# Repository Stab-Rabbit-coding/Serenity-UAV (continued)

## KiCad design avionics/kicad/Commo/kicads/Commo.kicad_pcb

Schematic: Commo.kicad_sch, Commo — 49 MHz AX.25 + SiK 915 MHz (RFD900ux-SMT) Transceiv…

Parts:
1.2k C: 10nF RX RC Bandpass 1200Hz Cap
1.2k R: 13k Ohm RX RC Bandpass 1200Hz
2.2k C: 10nF RX RC Bandpass 2200Hz Cap
2.2k R: 7.2k Ohm RX RC Bandpass 2200Hz
49M DDS: Si5351A-B-GT 49MHz DDS I2C Synthesiser
+3V 10n: 10nF C0G 0402 +3V3 VHF 49MHz Bypass
+3V 10u: 10uF X5R 0805 +3V3 Mid-freq
+3V 100n: 100nF X7R 0402 +3V3 HF Bypass
+3V 100u: 100uF 10V X5R 1210 +3V3 Bulk
+5V 100n: 100nF X7R 0402 +5V HF Bypass
+5V 100u: 100uF 10V X5R 1210 +5V Bulk
+5V Bead: 742792512
AFSK Cp: 1uF AFSK Audio Coupling DAC→PA
ANT CMC: SRF2012-100Y
ANT RPSMA: RPSMA-EDGE-50R
ANT TVS: PRTR5V0U2X; SOT-143
C1 120p: 120pF C0G LPF Shunt-1
C2 180p: 180pF C0G LPF Shunt-2
C3 120p: 120pF C0G LPF Shunt-3
C-SIK1: 10uF 10V X5R
C-SIK2: 100nF
C-SIK-SH1, C-SIK-SH2: DNP
CMP By: 100nF +3V3 U2B CMP Bypass
C_INV: 100nF C0G 0402 INV1 VCC Bypass
C_MUX: 100nF C0G 0402 MUX1 VCC Bypass
C_TPM_EMMA1: 100nF; C_0402_1005Metric
D-ANT-SIK: ESD101-B1-02ELS; Infineon_TSSLP-2-4_0.62x0.32mm
DAC By: 100nF +3V3 U2A DAC Bypass
ETH-PHY: ADIN1300BCPZ
GND X2Y: 4.7nF_X2Y_C0G
INV1: SN74LVC1G04 SOT-23-5 3.3V UART_RX_F->SBUS_OUT
J-ANT-SIK: MMCX vertical
J-ETH: JST-GH-4P-ETH
L1 100n: 100nH Coilcraft-0805HQ-101J LPF Series-1
L2 180n: 180nH Coilcraft-0805HQ-181J LPF Series-2
L3 180n: 180nH Coilcraft-0805HQ-181J LPF Series-3
L-SIK-SER: 0R link
LDO 3V3: MCP1703T-3302 LDO 3.3V 72dB-PSRR@100kHz
LDO By: 100nF +3V3 U6 LDO Bypass
LNA: MGA-82563 LNA 2.4dB NF 50-6000MHz
LNA By: 100nF +3V3 U4 LNA Bypass
MUX1: SN74LVC1G3157DRYR; Texas_USON-6_1x1.45mm_P0.5mm_SMD
OSC By: 100nF +3V3 X1 TCXO Bypass
PA 100mW: 2N3866 NPN BJT PA Class-AB Final 100mW
PA By: 100nF +5V U3 PA VCC Bypass
PA By2: 1nF U3B Collector RF Bypass
PA Cb1: 100pF DDS-RF Coupling Cap to U3A
PA Cb2: 100pF PA Interstage Bypass
PA Drvr: PMBT2222A,215; SOT-23
PA Rb1: 10k Ohm U3A Base Bias Resistor
PA Rb2: 1k Ohm U3B Base Bias Resistor
PA Rc1: 100 Ohm U3A Collector Load
PA Re: 10 Ohm U3B Emitter Degeneration
PB2-P1: PB2I-P1-2x18
PB2-P2: PB2I-P2-2x18
PGND 10n: 10nF C0G 0402 GND-PGND Moat Bridge
PTT Bead: 742792510 0402 Ferrite Bead 600Ohm@100MHz
RSSI Hi: 10k Ohm RSSI Scale Upper
RSSI Lo: 10k Ohm RSSI Scale Lower
RSSI_CBY: 100nF RSSI_CMP VCC Bypass
RSSI_CMP: LMV331 RSSI Carrier-Detect Comparator
RSSI_RH: 100k RSSI DCD Threshold Upper
RSSI_RL: 100k RSSI DCD Threshold Lower
RX Bead: 742792510 0402 Ferrite Bead 600Ohm@100MHz
RX Demod: LM393 Comparator RX-AFSK Demodulator
R_MODE: 10k Ohm MODE_SEL Pull-Down UART=default
R_TPM_RST_EMMA: 10k; R_0402_1005Metric
S1: SPST-SMD OPEN=UART CLOSED=SBUS
SIK: RFD900ux-SMT
SMA ESD: SMAJ5.0A Bidirectional TVS 5V Antenna ESD
SW By: 100nF +3V3 U5 Switch Bypass
T-ETH: 749010012A
T/R Sw: PE4259-63 SPDT TX/RX Switch ≥35dB isolation
TCXO 25M: TG2520SMN 25MHz TCXO ±0.5ppm
TPM: Infineon SLB9672 TPM2.0; QFN-32-1EP_5x5mm_P0.5mm_EP3.45x3.45mm
TX Bead: 742792510 0402 Ferrite Bead 600Ohm@100MHz
TX DAC: MCP4921 12-bit SPI DAC TX-AFSK Audio
Th Hi: 10k Ohm LM393 Threshold Upper
Th Lo: 10k Ohm LM393 Threshold Lower
U1 ByA: 100nF +3V3 U1-VDDA Bypass
U1 ByB: 100nF +3V3 U1-VDD Bypass
UART CMC: SRF2012-100Y CMC UART TX/RX Pair 10uH
UART TVS: PRTR5V0U2X; SOT-143

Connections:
+3V3: 49M DDS.1 (+3V3), 49M DDS.10 (+3V3), +3V 10n.1 (+3V3), +3V 10u.1 (+3V3), +3V 100n.1 (+3V3), +3V 100u.1 (+3V3), CMP By.1 (+3V3), C_INV.1 (+3V3), C_MUX.1 (+3V3), C_TPM_EMMA1.1, DAC By.1 (+3V3), INV1.4 (+3V3), LDO 3V3.3 (+3V3), LDO 3V3.4 (+3V3), LDO By.1 (+3V3), LNA.4 (+3V3), LNA By.1 (+3V3), MUX1.5 (VCC), OSC By.1 (+3V3), PB2-P1.33 (+3V3), PB2-P1.34 (+3V3), RSSI_CBY.1 (+3V3), RSSI_CMP.2 (+3V3), RSSI_RH.1 (+3V3), RX Demod.2 (+3V3), R_TPM_RST_EMMA.1, S1.1 (+3V3), SW By.1 (+3V3), TCXO 25M.1 (+3V3), TCXO 25M.4 (+3V3), TPM.1 (VDD), TPM.8 (NCI/VDD), TPM.14 (VDD), TPM.22 (VDD), TX DAC.1 (+3V3), TX DAC.6 (+3V3), Th Hi.1 (+3V3), U1 ByA.1 (+3V3), U1 ByB.1 (+3V3)
+5V: +5V Bead.1 (+5V), PB2-P1.35 (+5V), PB2-P2.35 (+5V)
+5V_FILT: +5V 100n.1 (+5V_FILT), +5V 100u.1 (+5V_FILT), +5V Bead.2 (+5V_FILT), LDO 3V3.1 (+5V_FILT), PA By.1 (+5V_FILT), PA Rb1.1 (+5V_FILT), PA Rc1.1 (+5V_FILT)
AFSK_IN: AFSK Cp.2 (AFSK_IN), RX Demod.1 (AFSK_IN)
AFSK_OUT: AFSK Cp.1 (AFSK_OUT), TX DAC.7 (AFSK_OUT)
ANT: ANT CMC.1, ANT CMC.2, ANT RPSMA.1 (ANT), ANT TVS.2 (IO1), SMA ESD.1 (ANT), T/R Sw.1 (ANT)
COMP_IN: 1.2k C.1 (COMP_IN), 1.2k R.2 (COMP_IN), 2.2k C.1 (COMP_IN), 2.2k R.2 (COMP_IN), RX Demod.3 (COMP_IN), Th Lo.1 (COMP_IN)
DDS_CLK: 49M DDS.6 (DDS_CLK), TX DAC.3 (DDS_CLK)
DDS_DAT: 49M DDS.7 (DDS_DAT), TX DAC.4 (DDS_DAT)
DDS_FSYNC: PB2-P1.26 (DDS_FSYNC), TX DAC.2 (DDS_FSYNC)
DDS_RF: 49M DDS.3 (DDS_RF), PA Cb1.1 (DDS_RF), PA Drvr.1 (B), PA Rb1.2 (DDS_RF)
EMMA_ETH_LINE_RXN: J-ETH.4 (EMMA_ETH_LINE_RXN), T-ETH.8 (EMMA_ETH_LINE_RXN)
EMMA_ETH_LINE_RXP: J-ETH.3 (EMMA_ETH_LINE_RXP), T-ETH.7 (EMMA_ETH_LINE_RXP)
EMMA_ETH_LINE_TXN: J-ETH.2 (EMMA_ETH_LINE_TXN), T-ETH.6 (EMMA_ETH_LINE_TXN)
EMMA_ETH_LINE_TXP: J-ETH.1 (EMMA_ETH_LINE_TXP), T-ETH.5 (EMMA_ETH_LINE_TXP)
EMMA_ETH_RXN: ETH-PHY.5 (EMMA_ETH_RXN), T-ETH.4 (EMMA_ETH_RXN)
EMMA_ETH_RXP: ETH-PHY.4 (EMMA_ETH_RXP), T-ETH.3 (EMMA_ETH_RXP)
EMMA_ETH_TXN: ETH-PHY.2 (EMMA_ETH_TXN), T-ETH.2 (EMMA_ETH_TXN)
EMMA_ETH_TXP: ETH-PHY.1 (EMMA_ETH_TXP), T-ETH.1 (EMMA_ETH_TXP)
GND: 1.2k C.2 (GND), 2.2k C.2 (GND), 49M DDS.2 (GND), 49M DDS.4 (GND), 49M DDS.5 (GND), 49M DDS.9 (GND), +3V 10n.2 (GND), +3V 10u.2 (GND), +3V 100n.2 (GND), +3V 100u.2 (GND), +5V 100n.2 (GND), +5V 100u.2 (GND), ANT RPSMA.2 (GND), ANT RPSMA.3 (GND), ANT TVS.1 (GND), ANT TVS.4 (VCC), C1 120p.2 (GND), C2 180p.2 (GND), C3 120p.2 (GND), C-SIK1.2 (N), C-SIK2.2 (N), C-SIK-SH1.2 (B), C-SIK-SH2.2 (B), CMP By.2 (GND), C_INV.2 (GND), C_MUX.2 (GND), C_TPM_EMMA1.2, D-ANT-SIK.2 (A2), DAC By.2 (GND), ETH-PHY.3 (GND), ETH-PHY.6 (GND), ETH-PHY.10 (GND), ETH-PHY.11 (GND), ETH-PHY.12 (GND), ETH-PHY.49 (GND), GND X2Y.1, GND X2Y.2, INV1.2 (GND), J-ANT-SIK.2 (SHIELD), LDO 3V3.2 (GND), LDO 3V3.5 (GND), LDO By.2 (GND), LNA.5 (GND), LNA.6 (GND), LNA By.2 (GND), MUX1.2 (GND), OSC By.2 (GND), PA By.2 (GND), PA By2.2 (GND), PA Cb2.2 (GND), PA Drvr.2 (E), PA Re.2 (GND), PB2-P1.1 (GND), PB2-P1.2 (GND), PB2-P1.36 (GND), PB2-P2.36 (GND), PGND 10n.1, PGND 10n.2, RSSI Lo.2 (GND), RSSI_CBY.2 (GND), RSSI_CMP.4 (GND), RSSI_RL.2 (GND), RX Demod.4 (GND), RX Demod.5 (GND), R_MODE.2 (GND), SIK.8 (GND), SIK.9 (GND), SIK.11 (GND), SIK.12 (GND), SIK.14 (GND), SIK.15 (GND), SIK.17 (GND), SIK.18 (GND), SIK.20 (GND), SIK.29 (GND), SIK.30 (GND), SMA ESD.2 (GND), SW By.2 (GND), T/R Sw.2 (GND), T/R Sw.6 (GND), TCXO 25M.2 (GND), TPM.2 (GND), TPM.9 (GND), TPM.16 (NCI/GND), TPM.23 (GND), TPM.32 (GND), TX DAC.5 (GND), TX DAC.8 (GND), Th Hi.2 (GND), Th Lo.2 (GND), U1 ByA.2 (GND), U1 ByB.2 (GND), UART TVS.1 (GND), UART TVS.4 (VCC)
GND2_ETH: ETH-PHY.21 (GND2_ETH), ETH-PHY.22 (GND2_ETH), ETH-PHY.25 (GND2_ETH), ETH-PHY.34 (GND2_ETH), ETH-PHY.36 (GND2_ETH)
MDC: ETH-PHY.19 (MDC), PB2-P2.18 (MDC)
MDIO: ETH-PHY.18 (MDIO), PB2-P2.17 (MDIO)
MODE_SEL: MUX1.6 (S), R_MODE.1 (MODE_SEL), S1.2 (MODE_SEL)
PA_EMIT: PA 100mW.2 (GND), PA Re.1 (PA_EMIT)
PA_INT: PA 100mW.1 (PA_INT), PA Cb1.2 (PA_INT), PA Cb2.1 (PA_INT), PA Drvr.3 (C), PA Rb2.1, PA Rb2.2, PA Rc1.2 (PA_INT)
PHY2_INTRN: ETH-PHY.20 (PHY2_INTRN), PB2-P2.14 (PHY2_INTRN)
PHY2_RSTN: ETH-PHY.35 (PHY2_RSTN), PB2-P2.13 (PHY2_RSTN)
PTT_N: PB2-P2.1 (PTT_N), PTT Bead.1, PTT Bead.2, T/R Sw.4 (PTT_N)
RF_FILT: C3 120p.1 (RF_FILT), L3 180n.2 (RF_FILT), T/R Sw.5 (RF_FILT)
RF_LPF_N1: C1 120p.1 (RF_LPF_N1), L1 100n.2 (RF_LPF_N1), L2 180n.1 (RF_LPF_N1)
RF_LPF_N2: C2 180p.1 (RF_LPF_N2), L2 180n.2 (RF_LPF_N2), L3 180n.1 (RF_LPF_N2)
RF_RX: LNA.3 (RF_RX), T/R Sw.3 (RF_RX)
RF_TX: ANT TVS.3 (IO2), L1 100n.1 (RF_TX), PA 100mW.3 (RF_TX), PA By2.1 (RF_TX)
RMII1_CRS_DV: ETH-PHY.32 (RMII1_CRS_DV), PB2-P2.21 (RMII1_CRS_DV)
RMII1_REF_CLK: ETH-PHY.29 (RMII1_REF_CLK), PB2-P2.19 (RMII1_REF_CLK)
RMII1_RXD0: ETH-PHY.30 (RMII1_RXD0), PB2-P2.23 (RMII1_RXD0)
RMII1_RXD1: ETH-PHY.31 (RMII1_RXD1), PB2-P2.22 (RMII1_RXD1)
RMII1_RX_ER: ETH-PHY.33 (RMII1_RX_ER), PB2-P2.20 (RMII1_RX_ER)
RMII1_TXD0: ETH-PHY.28 (RMII1_TXD0), PB2-P2.26 (RMII1_TXD0)
RMII1_TXD1: ETH-PHY.27 (RMII1_TXD1), PB2-P2.25 (RMII1_TXD1)
RMII1_TX_EN: ETH-PHY.26 (RMII1_TX_EN), PB2-P2.24 (RMII1_TX_EN)
RSSI_ANA: RSSI Hi.2 (RSSI_ANA), RSSI Lo.1 (RSSI_ANA), RSSI_CMP.1 (RSSI_ANA)
RSSI_DCD: PB2-P2.2 (RSSI_DCD), RSSI_CMP.5 (RSSI_DCD)
RSSI_RAW: LNA.2 (RSSI_RAW), RSSI Hi.1 (RSSI_RAW)
RSSI_REF: RSSI_CMP.3 (RSSI_REF), RSSI_RH.2 (RSSI_REF), RSSI_RL.1 (RSSI_REF)
RX_LNA: 1.2k R.1 (RX_LNA), 2.2k R.1 (RX_LNA), LNA.1 (RX_LNA)
SBUS_OUT: INV1.3 (SBUS_OUT), MUX1.1 (B2)
SIK_ANT_F: C-SIK-SH2.1 (A), D-ANT-SIK.1 (A1), J-ANT-SIK.1 (RF), L-SIK-SER.2 (B)
SIK_ANT_RF: C-SIK-SH1.1 (A), L-SIK-SER.1 (A), SIK.13 (SIK_ANT_RF)
SIK_CTS: PB2-P1.20 (LORA_DIO0), SIK.28 (SIK_CTS)
SIK_RTS: PB2-P1.19 (LORA_RESETN), SIK.27 (SIK_RTS)
SIK_VCC: C-SIK1.1, C-SIK2.1, SIK.19 (SIK_VCC)
SPI1_CLK: PB2-P1.25 (SPI1_CLK), TPM.19 (SCLK)
SPI1_CS_TPM: PB2-P1.21 (SPI1_CS_TPM), TPM.20 (CS#)
SPI1_MISO: PB2-P1.23 (SPI1_MISO), TPM.24 (MISO)
SPI1_MOSI: PB2-P1.24 (SPI1_MOSI), TPM.21 (MOSI)
TCXO_OUT: 49M DDS.8 (TCXO_OUT), TCXO 25M.3 (TCXO_OUT)
TPM_IRQN: PB2-P2.12 (TPM_IRQN), TPM.18 (PIRQ#)
TPM_RSTN: PB2-P2.11 (TPM_RSTN), R_TPM_RST_EMMA.2, TPM.17 (RST#)
UART_49MHZ_XCVR_RX: PB2-P1.15 (UART_49MHZ_XCVR_RX), UART CMC.1 (UART_49MHZ_XCVR_RX), UART TVS.2 (IO1)
UART_49MHZ_XCVR_TX: PB2-P1.16 (UART_49MHZ_XCVR_TX), UART CMC.4 (UART_49MHZ_XCVR_TX), UART TVS.3 (IO2)
UART_RX_F: INV1.1 (UART_RX_F), MUX1.3 (B1), RX Bead.1, RX Bead.2
UART_RX_MUX: MUX1.4 (A), UART CMC.3 (UART_RX_MUX)
UART_SIK_RX: PB2-P1.17 (UART_SIK_RX), SIK.25 (UART_SIK_RX)
UART_SIK_TX: PB2-P1.18 (UART_SIK_TX), SIK.26 (UART_SIK_TX)
UART_TX_F: TX Bead.1, TX Bead.2, UART CMC.2 (UART_TX_F)
VCC2_ETH: ETH-PHY.7 (VCC2_ETH), ETH-PHY.8 (VCC2_ETH), ETH-PHY.9 (VCC2_ETH), ETH-PHY.40 (VCC2_ETH), ETH-PHY.41 (VCC2_ETH)

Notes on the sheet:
POWER SUPPLY (5V input filter, MCP1703 LDO, bypass cascade)
DDS / TCXO (Si5351A 49 MHz synthesiser)
PA CHAIN (MMBT2222A driver + 2N3866 100 mW final)
6-ELEMENT CHEBYSHEV LPF
T/R SWITCH, LNA, ANTENNA PORT
AFSK MODEM (MCP4921 TX DAC, LM393 RX demod, tone filters)
UART / SBUS DIGITAL (CMC, TVS, beads, inverter, mux)
RSSI CARRIER-DETECT (NEW 2026-07-04 — analog RSSI -> 1-bit RSSI_DCD)
SiK RFD900ux-SMT (915 MHz UHF telemetry -- relocated from XO 2026-09-21, see avionics/WBS.md)
ETHERNET 2nd PORT (ADIN1300 PHY + T-ETH isolation xfmr, JST-GH-4P line)
PB2-I PASSTHROUGH RAILS (PocketBeagle 2 Industrial P1 + P2)
=== Section: TPM (SLB9672, added 2026-07-26; binds to the PB2-I host -- SPI1 shared bus + TPM_IRQN/TPM_RSTN via P1/P2, no dedicated header) ===
WÜRTH ELEKTRONIK USAGE NOTICE (verbatim, 749010012A data sheet rev 004.000 p.1; applies to Würth parts on this board: 749010012A, 742792510, 742792512): This electronic component has been designed and developed for usage in general electronic equipment only. This product is not authorized for use i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

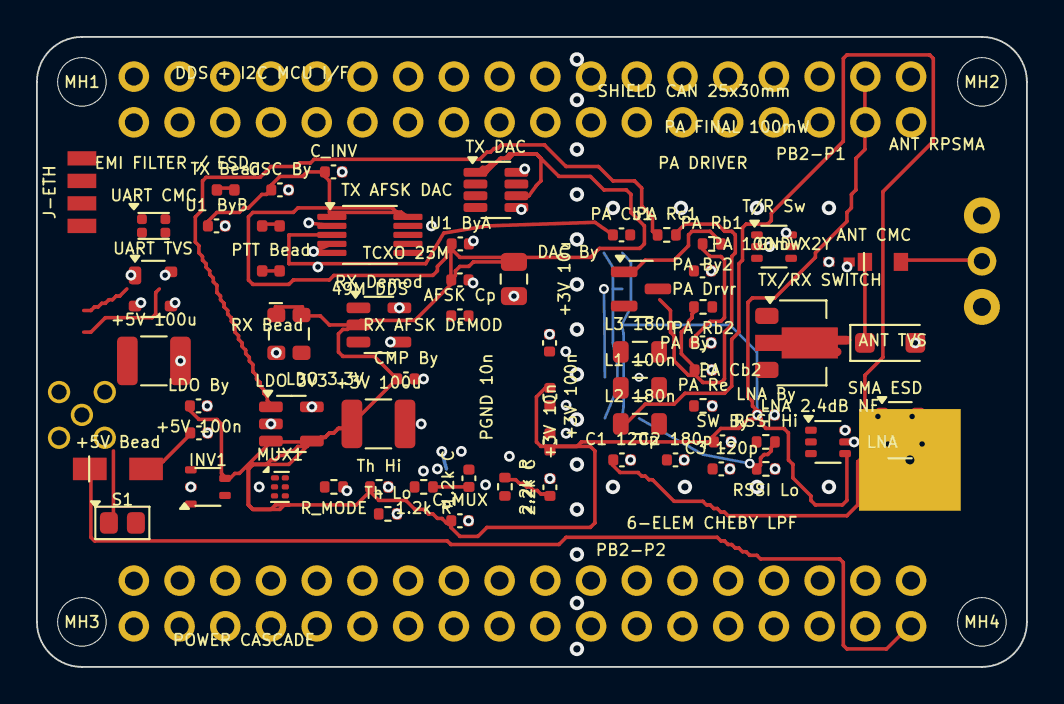
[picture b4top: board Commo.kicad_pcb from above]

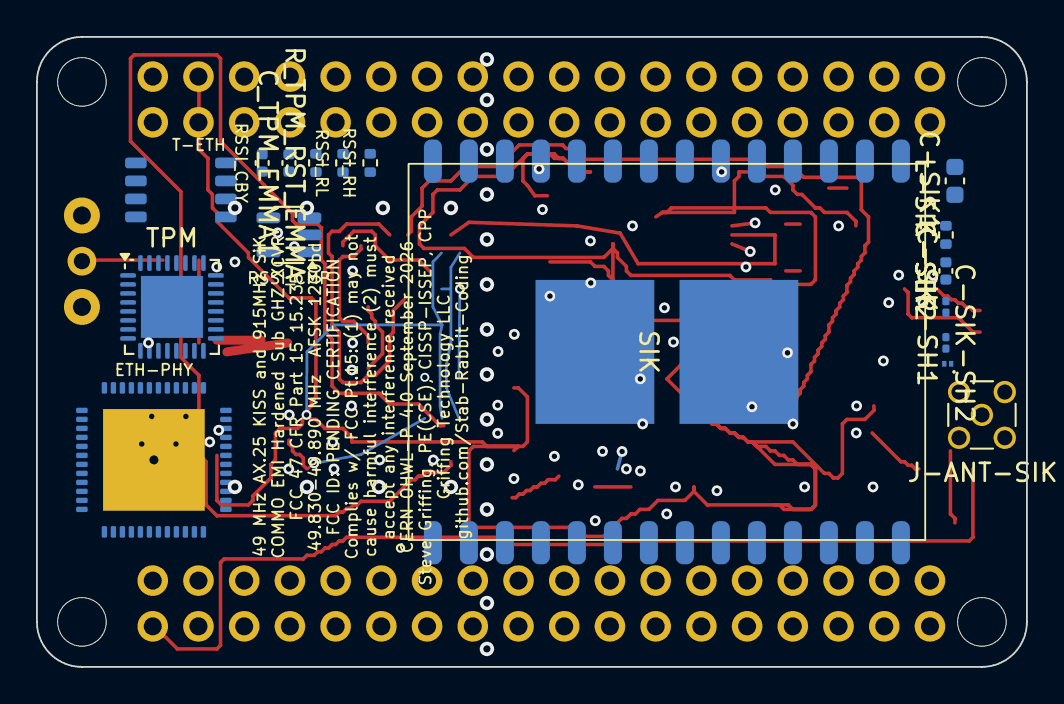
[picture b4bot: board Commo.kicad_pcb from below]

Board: 4 copper layers, 55.0 x 35.0 mm, 88 parts (17 on the bottom side), 68 nets.

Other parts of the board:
MH1, MH2, MH3, MH4: MountingHole_2.7mm_M2.5

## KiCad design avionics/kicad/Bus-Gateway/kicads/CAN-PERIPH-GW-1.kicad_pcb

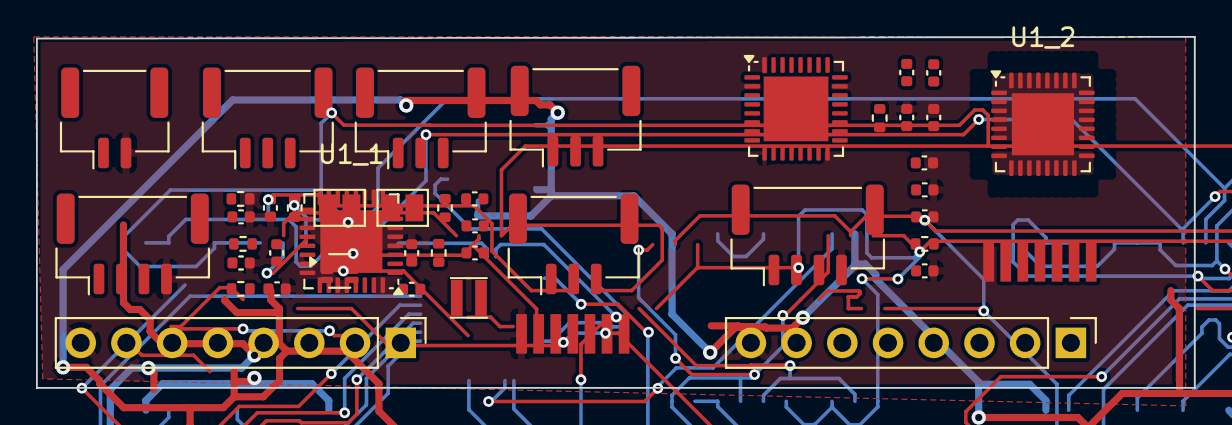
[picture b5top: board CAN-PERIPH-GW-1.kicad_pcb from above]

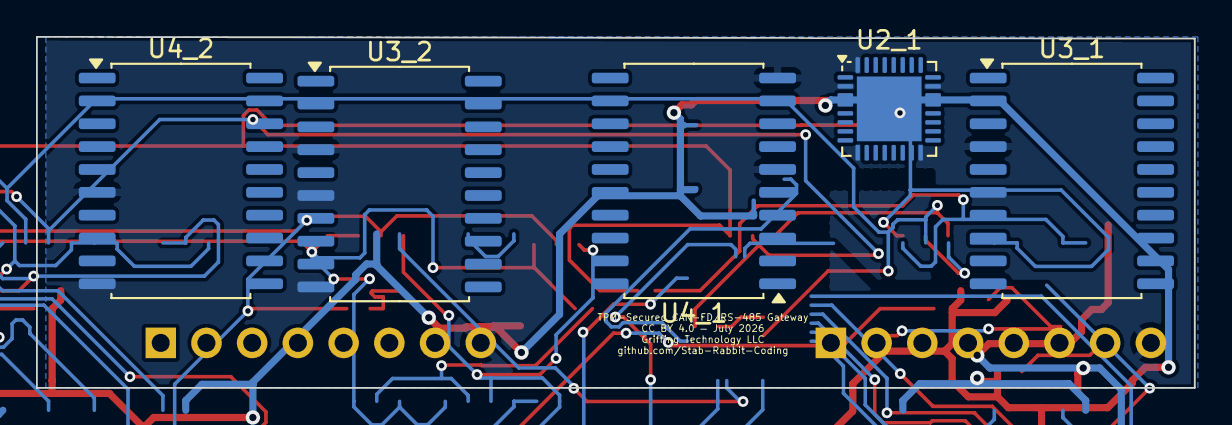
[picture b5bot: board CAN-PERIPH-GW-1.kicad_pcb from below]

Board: 2 copper layers, 64.3 x 19.5 mm, 49 parts (6 on the bottom side), 71 nets.

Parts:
C_IN: 10uF; C_0402_1005Metric
C_ISO1_1, C_ISO1_2: 100nF; C_0402_1005Metric
C_ISO2_1, C_ISO2_2: 1uF; C_0402_1005Metric
C_MCU1_1, C_MCU1_2: 100nF; C_0402_1005Metric
C_OUT: 22uF; C_0402_1005Metric
C_RS1_1, C_RS1_2, C_RS2_1, C_RS2_2: 100nF; C_0402_1005Metric
C_TPM1_1, C_TPM1_2: 100nF; C_0402_1005Metric
C_TPM2_1, C_TPM2_2: 1uF; C_0402_1005Metric
C_VCORE_1, C_VCORE_2: 1uF; C_0402_1005Metric
J_CAN_IN: CAN-FD IN; JST_GH_BM03B-GHS-TBT_1x03-1MP_P1.25mm_Vertical
J_CAN_OUT: CAN-FD OUT; JST_GH_BM03B-GHS-TBT_1x03-1MP_P1.25mm_Vertical
J_ENC_1, J_ENC_2: AK7455 pigtail; Pigtail_7W_DirectSolder
J_FLEX_1, J_FLEX_2: UART/TTL/PWM/BSHOT; PinHeader_1x08_P2.54mm_Vertical
J_PWR: +5V/GND; JST_GH_BM02B-GHS-TBT_1x02-1MP_P1.25mm_Vertical
J_RS485_IN: RS485 IN; JST_GH_BM03B-GHS-TBT_1x03-1MP_P1.25mm_Vertical
J_RS485_OUT: RS485 OUT; JST_GH_BM03B-GHS-TBT_1x03-1MP_P1.25mm_Vertical
J_SWD_1, J_SWD_2: SWD; JST_GH_BM04B-GHS-TBT_1x04-1MP_P1.25mm_Vertical
L1: 2.2uH; L_Taiyo-Yuden_NR-20xx
R_485TERM: 120R; R_0402_1005Metric
R_CANTERM: 120R; R_0402_1005Metric
R_FBB: 100k 1%; R_0402_1005Metric
R_FBT: 453k 1%; R_0402_1005Metric
R_NRST_1, R_NRST_2: 10k; R_0402_1005Metric
R_TPM_RST_1, R_TPM_RST_2: 10k; R_0402_1005Metric
SJ1, SJ2: open; SolderJumper-2_P1.3mm_Open_Pad1.0x1.5mm
U1_1, U1_2: TI MSPM0G3518-Q1; Texas_RHB0032E_VQFN-32-1EP_5x5mm_P0.5mm_EP3.45x3.45mm
U2_1, U2_2: Infineon SLB 9672AU2.0; QFN-32-1EP_5x5mm_P0.5mm_EP3.6x3.6mm
U3_1, U3_2: ISOW1044BDFMR; SOIC-20W_7.5x12.8mm_P1.27mm
U4_1, U4_2: ISOW1412; SOIC-20W_7.5x12.8mm_P1.27mm
U_REG_3V3: TLV62569PDRLR; SOT-563

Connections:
+3V3: C_ISO1_1.1, C_ISO1_2.1, C_MCU1_1.1, C_MCU1_2.1, C_OUT.1, C_RS1_1.1, C_RS1_2.1, C_TPM1_1.1, C_TPM1_2.1, C_TPM2_1.1, C_TPM2_2.1, J_ENC_1.6, J_ENC_2.6, J_FLEX_1.7, J_FLEX_2.7, L1.2, R_FBT.1, R_NRST_1.1, R_NRST_2.1, R_TPM_RST_1.1, R_TPM_RST_2.1, U1_1.4, U1_2.4, U2_1.1, U2_1.8, U2_1.14, U2_1.22, U2_2.1, U2_2.8, U2_2.14, U2_2.22, U3_1.1, U3_1.9, U3_2.1, U3_2.9, U4_1.1, U4_1.9, U4_2.1, U4_2.9
+5V: C_IN.1, J_FLEX_1.6, J_FLEX_2.6, J_PWR.1, U_REG_3V3.3, U_REG_3V3.5
CANFD_FLT_N_1: U1_1.27, U3_1.8
CANFD_FLT_N_2: U1_2.27, U3_2.8
CANFD_RX_1: U1_1.17, U3_1.5
CANFD_RX_2: U1_2.17, U3_2.5
CANFD_TX_1: U1_1.16, U3_1.3
CANFD_TX_2: U1_2.16, U3_2.3
CANTERM_MID: R_CANTERM.2, SJ1.1
CAN_H: J_CAN_IN.1, J_CAN_OUT.1, R_CANTERM.1, U3_1.19, U3_2.19
CAN_L: J_CAN_IN.2, J_CAN_OUT.2, SJ1.2, U3_1.18, U3_2.18
ENC_ERROR_1: J_ENC_1.7, U1_1.18
ENC_ERROR_2: J_ENC_2.7, U1_2.18
ENC_SPI_CS_1: J_ENC_1.2, U1_1.19
ENC_SPI_CS_2: J_ENC_2.2, U1_2.19
ENC_SPI_MISO_1: J_ENC_1.5, U1_1.20
ENC_SPI_MISO_2: J_ENC_2.5, U1_2.20
ENC_SPI_MOSI_1: J_ENC_1.4, U1_1.22
ENC_SPI_MOSI_2: J_ENC_2.4, U1_2.22
ENC_SPI_SCK_1: J_ENC_1.3, U1_1.21
ENC_SPI_SCK_2: J_ENC_2.3, U1_2.21
FLEX_BSHOT_IO_1: J_FLEX_1.5, U1_1.30
FLEX_BSHOT_IO_2: J_FLEX_2.5, U1_2.30
FLEX_PWM_IO_1: J_FLEX_1.4, U1_1.29
FLEX_PWM_IO_2: J_FLEX_2.4, U1_2.29
FLEX_TTL_GPIO_1: J_FLEX_1.3, U1_1.28
FLEX_TTL_GPIO_2: J_FLEX_2.3, U1_2.28
FLEX_UART_RX_1: J_FLEX_1.2, U1_1.2
FLEX_UART_RX_2: J_FLEX_2.2, U1_2.2
FLEX_UART_TX_1: J_FLEX_1.1, U1_1.1
FLEX_UART_TX_2: J_FLEX_2.1, U1_2.1
GND: C_IN.2, C_ISO1_1.2, C_ISO1_2.2, C_MCU1_1.2, C_MCU1_2.2, C_OUT.2, C_RS1_1.2, C_RS1_2.2, C_TPM1_1.2, C_TPM1_2.2, C_TPM2_1.2, C_TPM2_2.2, C_VCORE_1.2, C_VCORE_2.2, J_ENC_1.1, J_ENC_2.1, J_FLEX_1.8, J_FLEX_2.8, J_PWR.2, J_SWD_1.4, J_SWD_2.4, R_FBB.2, U1_1.5, U1_1.33, U1_2.5, U1_2.33, U2_1.2, U2_1.9, U2_1.16, U2_1.23, U2_1.32, U2_1.33, U2_2.2, U2_2.9, U2_2.16, U2_2.23, U2_2.32, U2_2.33, U3_1.4, U3_1.6, U3_1.10, U3_2.4, U3_2.6, U3_2.10, U4_1.6, U4_1.10, U4_2.6, U4_2.10, U_REG_3V3.2
ISO_3V3_485_1: C_RS2_1.1, U4_1.12, U4_1.16
ISO_3V3_485_2: C_RS2_2.1, U4_2.12, U4_2.16
ISO_5V_CAN_1: C_ISO2_1.1, U3_1.12, U3_1.13, U3_1.20
ISO_5V_CAN_2: C_ISO2_2.1, U3_2.12, U3_2.13, U3_2.20
ISO_GND_485: C_RS2_1.2, C_RS2_2.2, J_RS485_IN.3, J_RS485_OUT.3, U4_1.11, U4_1.13, U4_1.15, U4_2.11, U4_2.13, U4_2.15
ISO_GND_CAN: C_ISO2_1.2, C_ISO2_2.2, J_CAN_IN.3, J_CAN_OUT.3, U3_1.11, U3_1.15, U3_1.16, U3_1.17, U3_2.11, U3_2.15, U3_2.16, U3_2.17
MCU_NRST_1: J_SWD_1.3, R_NRST_1.2, U1_1.3
MCU_NRST_2: J_SWD_2.3, R_NRST_2.2, U1_2.3
MCU_SWCLK_1: J_SWD_1.2, U1_1.24
MCU_SWCLK_2: J_SWD_2.2, U1_2.24
MCU_SWDIO_1: J_SWD_1.1, U1_1.23
MCU_SWDIO_2: J_SWD_2.1, U1_2.23
MCU_VCORE_1: C_VCORE_1.1, U1_1.32
MCU_VCORE_2: C_VCORE_2.1, U1_2.32
RS485_A: J_RS485_IN.1, J_RS485_OUT.1, R_485TERM.1, U4_1.17, U4_1.20, U4_2.17, U4_2.20
RS485_B: J_RS485_IN.2, J_RS485_OUT.2, SJ2.2, U4_1.18, U4_1.19, U4_2.18, U4_2.19
RS485_DE_1: U1_1.25, U4_1.3, U4_1.5
RS485_DE_2: U1_2.25, U4_2.3, U4_2.5
RS485_FLT_N_1: U1_1.26, U4_1.8
RS485_FLT_N_2: U1_2.26, U4_2.8
RS485_RX_1: U1_1.13, U4_1.4
RS485_RX_2: U1_2.13, U4_2.4
RS485_TX_1: U1_1.12, U4_1.2
RS485_TX_2: U1_2.12, U4_2.2
TERM485_MID: R_485TERM.2, SJ2.1
TPM_PIRQ_1: U1_1.7, U2_1.18
TPM_PIRQ_2: U1_2.7, U2_2.18
TPM_RESET_N_1: R_TPM_RST_1.2, U1_1.11, U2_1.17
TPM_RESET_N_2: R_TPM_RST_2.2, U1_2.11, U2_2.17
TPM_SPI_CS_1: U1_1.6, U2_1.20
TPM_SPI_CS_2: U1_2.6, U2_2.20
TPM_SPI_MISO_1: U1_1.8, U2_1.24
TPM_SPI_MISO_2: U1_2.8, U2_2.24
TPM_SPI_MOSI_1: U1_1.9, U2_1.21
TPM_SPI_MOSI_2: U1_2.9, U2_2.21
TPM_SPI_SCK_1: U1_1.10, U2_1.19
TPM_SPI_SCK_2: U1_2.10, U2_2.19
U_REG_FB: R_FBB.1, R_FBT.2, U_REG_3V3.1
U_REG_SW: L1.1, U_REG_3V3.4

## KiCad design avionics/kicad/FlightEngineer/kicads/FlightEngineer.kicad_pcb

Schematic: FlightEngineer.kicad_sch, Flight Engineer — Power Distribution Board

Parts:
C1, C2: 220uF 35V; CP_Radial_D10.0mm_P5.00mm; MPN EEF-CX1V221R
C3: 100nF X7R 0805; C_0805_2012Metric
CM1, CM2: 7440640500; Wurth_7440640500_CMC_THT; MPN 7440640500
CM_ESC1, CM_ESC2, CM_ESC3, CM_ESC4: 7440640500; Wurth_7440640500_CMC_THT; MPN 7440640500
C_BEC1_BOOT, C_BEC1_OUT2, C_BEC2_BOOT, C_BEC2_OUT2, C_BEC6_BOOT: 100nF; C_0402_1005Metric
C_BEC1_COMP, C_BEC2_COMP: 2.2nF; C_0402_1005Metric
C_BEC1_IN, C_BEC2_IN: 100uF 50V; C_1210_3225Metric
C_BEC1_OUT1, C_BEC2_OUT1: 220uF; C_1210_3225Metric
C_BEC1_SS, C_BEC2_SS: 10nF; C_0402_1005Metric
C_BEC6_COMP: 1nF; C_0402_1005Metric
C_BEC_SV_IN: 100uF 50V; C_1210_3225Metric
C_BEC_SV_OUT1: 100uF; C_1210_3225Metric
C_BEC_SV_OUT2: 100nF; C_0402_1005Metric
C_CAP1, C_CAP2: 0.1uF; C_0402_1005Metric
C_DEC1, C_DEC2, C_DEC3, C_DEC4: 470uF 35V low-ESR; CP_Radial_D10.0mm_P5.00mm; MPN EEUFC1V471
C_DM1: 10uF 50V X7R 1210; C_1210_3225Metric; MPN 885012207016
C_H_IN: 10uF; C_0805_2012Metric
C_H_OUT: 22uF; C_0805_2012Metric
C_ISOCAN1, C_ISOCAN4: 10nF; C_0402_1005Metric
C_ISOCAN2, C_ISOCAN5: 10uF; C_0805_2012Metric
C_ISOCAN3: 100nF; C_0402_1005Metric
C_MCU_3V3: 100nF; C_0402_1005Metric
C_MCU_VCORE: 1uF; C_0402_1005Metric
C_NTC: 100nF X7R; C_0402_1005Metric
C_REGOUT: 1uF; C_0402_1005Metric
C_RS485_1, C_RS485_4: 10nF; C_0402_1005Metric
C_RS485_2, C_RS485_5: 10uF; C_0805_2012Metric
C_RS485_3: 100nF; C_0402_1005Metric
C_TPM1: 1uF; C_0402_1005Metric
C_TPM2, C_TPM3, C_TPM4: 100nF; C_0402_1005Metric
C_Y1, C_Y2: 4.7nF 250V Y2; C_0805_2012Metric; MPN SA305E472MAR
D1: SMBJ33CA; D_SMB; MPN SMBJ33CA
D_I2C: PRTR5V0U2X; SOT-363_SC-70-6; MPN PRTR5V0U2X,115
D_OR1, D_OR2: MBRD1045CT; TO-263-3_TabPin2; MPN MBRD1045CT
ESC1_LINK, ESC2_LINK, ESC3_LINK, ESC4_LINK: 0R link; R_0603_1608Metric
F1: 0297150.ZXNV 150A MAXI; MAXI_Blade_Fuseholder_2P; MPN 0297150.ZXNV
FB_5V1, FB_5V2, FB_6V: 742792612; L_1210_3225Metric; MPN 742792612
F_ESC1, F_ESC2, F_ESC3, F_ESC4: 0297040.WXNV 40A mini; Fuseholder_Blade_Mini_Keystone_3568; MPN 0297040.WXNV
J_5V, J_6V: Nano-Fit 4P; Molex_Nano-Fit_105309-xx04_1x04_P2.50mm_Vertical; MPN WM1720-ND
J_485_IN, J_485_OUT: SM03B-GHS-TB; JST_GH_SM03B-GHS-TB_1x03-1MP_P1.25mm_Horizontal; MPN SM03B-GHS-TB(LF)(SN)
J_ALERT: SM02B-GHS-TB; JST_GH_SM02B-GHS-TB_1x02-1MP_P1.25mm_Horizontal; MPN SM02B-GHS-TB(LF)(SN)
J_BAL: XH-7P; JST_XH_B7B-XH-A_1x07_P2.50mm_Vertical
J_BATT: XT60PW-F; AMASS_XT60PW-F_1x02_P7.20mm_Horizontal; MPN XT60PW-F
J_CAN_IN: SM03B-GHS-TB; JST_GH_SM03B-GHS-TB_1x03-1MP_P1.25mm_Horizontal; MPN SM03B-GHS-TB(LF)(SN)
J_CAN_OUT: SM03B-GHS-TB; JST_GH_SM03B-GHS-TB_1x03-1MP_P1.25mm_Horizontal; MPN SM03B-GHS-TB(LF)(SN)
J_CHASSIS: M3 standoff x4; M3_Chassis_Lug_PGND; MPN 94459A120
J_ESC1, J_ESC2, J_ESC3, J_ESC4: XT30PW-F; AMASS_XT30PW-F_1x02_P2.50mm_Horizontal; MPN XT30PW-F
J_I2C: SM04B-GHS-TB; JST_GH_SM04B-GHS-TB_1x04-1MP_P1.25mm_Horizontal; MPN SM04B-GHS-TB(LF)(SN)
J_NTC: SM02B-GHS-TB; JST_GH_SM02B-GHS-TB_1x02-1MP_P1.25mm_Horizontal; MPN SM02B-GHS-TB(LF)(SN)
J_PGND_BATT: M3 chassis lug; M3_Chassis_Lug_PGND; MPN 94459A120
J_SHLD_5V, J_SHLD_6V: PGND via; PGND_ViaPad_1p2mm
J_SHLD_ALERT: PGND via; PGND_ViaPad_1p2mm
J_SHLD_ESC1, J_SHLD_ESC2, J_SHLD_ESC3, J_SHLD_ESC4: M3 chassis lug; M3_Chassis_Lug_PGND; MPN 94459A120
J_SHLD_I2C: PGND via; PGND_ViaPad_1p2mm
J_SHLD_NTC: PGND via; PGND_ViaPad_1p2mm
J_SWD_H: SM04B-GHS-TB; JST_GH_SM04B-GHS-TB_1x04-1MP_P1.25mm_Horizontal; MPN SM04B-GHS-TB(LF)(SN)
L1, L2, L3: 10uH 6A; L_1210_3225Metric; MPN 744314100
L_H1: 2.2uH; L_1210_3225Metric
Q_BATT_CHG: AON6260 (DNP); AOSMD_DFN5x6-8L; MPN AON6260; not fitted
Q_BATT_DSG: AON6260; AOSMD_DFN5x6-8L; MPN AON6260
RS1, RS2, RS3, RS4: 1mOhm 3W Kelvin; R_Shunt_Vishay_WSK2512_6332Metric_T1.19mm; MPN CSS2H-2512K-1L00F
RS_MAIN: 1mOhm 5W Kelvin; R_Shunt_Vishay_WSK2512_6332Metric_T1.19mm; MPN CSS2H-2512K-1L00F
R_485TERM: 120R; R_0603_1608Metric; not fitted
R_ALERT: 2.2k; R_0402_1005Metric
R_BAL1, R_BAL2, R_BAL3, R_BAL4, R_BAL5, R_BAL6: 100R; R_0402_1005Metric
R_CANSTB: 0R; R_0402_1005Metric
R_CANTERM: 120R; R_0603_1608Metric; not fitted
R_CHGND: 0R socketed; R_0402_1005Metric
R_DSG_G: 10k; R_0402_1005Metric
R_EN_BIAS: 100k; R_0402_1005Metric
R_FB1_1, R_FB2_1: 56.2k 1%; R_0402_1005Metric
R_FB1_2, R_FB2_2, R_FB6_2: 10.0k 1%; R_0402_1005Metric
R_FB6_1: 64.9k 1%; R_0402_1005Metric
R_GND_PGND: 0R; R_0603_1608Metric
R_H_FBB: 100k 1%; R_0402_1005Metric
R_H_FBT: 453k 1%; R_0402_1005Metric
R_I2C_SCL, R_I2C_SDA: 4.7k; R_0402_1005Metric
R_MCU_NRST: 10k; R_0402_1005Metric
R_NTC_PU: 10k; R_0402_1005Metric
R_RS485FLT_PU: 10k; R_0402_1005Metric
R_TPM10: 10k; R_0402_1005Metric
R_TPMCS: 10k; R_0402_1005Metric
U_BEC_5V_1, U_BEC_5V_2: TPS54620RGYT; Texas_RGY0014A_VQFN-14-1EP_3.5x3.5mm; MPN TPS54620RGYT
U_BEC_6V: TPS54540DDAR; TI_SO-PowerPAD-8; MPN TPS54540DDAR
U_CELL: BQ76930PWRQ1; TSSOP-30_4.4x7.8mm_P0.5mm; MPN BQ76930PWRQ1
U_IS1, U_IS2, U_IS3, U_IS4: INA226AIDGSR; VSSOP-10_3x3mm_P0.5mm; MPN INA226AIDGSR
U_ISOCAN: ISOW1044BDFMR; SOIC-20W_7.5x12.8mm_P1.27mm; MPN ISOW1044BDFMR
U_IS_MAIN: INA226AIDGSR; VSSOP-10_3x3mm_P0.5mm; MPN INA226AIDGSR
U_MCU: MSPM0G3518-Q1; Texas_RHB0032E_VQFN-32-1EP_5x5mm_P0.5mm_EP3.45x3.45mm; MPN M0G3518QRHBRQ1
U_REG_3V3_H: TLV62569PDRLR; SOT-563; MPN TLV62569DBVR
U_RS485: ISOW1412DFMR; SOIC-20W_7.5x12.8mm_P1.27mm; MPN ISOW1412DFMR
U_TPM: SLB9672XU20; QFN-32-1EP_5x5mm_P0.5mm_EP3.6x3.6mm; MPN SLB9672XU20FW1611XUMA1
VDIS_LINK: 0R link; R_0603_1608Metric

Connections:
+3V3: C_H_OUT.1, C_ISOCAN3.1, C_MCU_3V3.1, C_RS485_3.1, C_TPM1.1, C_TPM2.1, C_TPM3.1, C_TPM4.1, L_H1.2 (B), R_H_FBT.1, R_MCU_NRST.1 (A), R_RS485FLT_PU.1 (A), R_TPM10.1 (A), R_TPMCS.1 (A), U_ISOCAN.1 (VIO), U_MCU.4 (+3V3), U_RS485.1 (VIO), U_TPM.1 (VDD), U_TPM.14 (VDD), U_TPM.22 (VDD)
+3V3_BIAS_EN: R_EN_BIAS.2 (B), U_BEC_5V_1.10 (EN), U_BEC_5V_2.10 (EN), U_BEC_6V.3 (EN)
+5V: C_H_IN.1, C_ISOCAN1.1, C_ISOCAN2.1, C_RS485_1.1, C_RS485_2.1, D_I2C.4 (NC), D_I2C.5 (VCC), J_I2C.2 (+5V), R_ALERT.1 (A), R_I2C_SCL.1 (A), R_I2C_SDA.1 (A), U_IS1.6 (VS), U_IS2.2 (A0), U_IS2.6 (VS), U_IS3.6 (VS), U_IS4.6 (VS), U_ISOCAN.9 (VDD), U_IS_MAIN.1 (A1), U_IS_MAIN.6 (VS), U_REG_3V3_H.3 (VIN), U_REG_3V3_H.5 (EN), U_RS485.9 (VDD)
+5V_AVIONICS: D_OR1.2 (K), D_OR1.3 (K2), D_OR2.2 (K), D_OR2.3 (K2), J_5V.1 (+), J_5V.2 (+)
+5V_PRE_OR1: C_BEC1_OUT1.1, C_BEC1_OUT2.1, D_OR1.1 (A), L1.2 (B), R_FB1_1.1 (A)
+5V_PRE_OR2: C_BEC2_OUT1.1, C_BEC2_OUT2.1, D_OR2.1 (A), L2.2 (B), R_FB2_1.1 (A)
+6V_SERVO: C_BEC_SV_OUT1.1, C_BEC_SV_OUT2.1, J_6V.1 (+), J_6V.2 (+), L3.2 (B), R_FB6_1.1 (A)
BATT_CM1_N: CM1.4 (P2B), CM2.3 (P2A)
BATT_CM1_P: CM1.2 (P1B), CM2.1 (P1A)
BATT_DSG_GATE: R_DSG_G.1 (A), U_CELL.1 (DSG)
BATT_DSG_GATE_R: Q_BATT_DSG.4 (G), R_DSG_G.2 (B)
BATT_RAW_N: CM1.3 (P2A), J_BATT.2 (-)
BATT_RAW_P: CM1.1 (P1A), J_BATT.1 (+)
BEC1_BOOT: C_BEC1_BOOT.1, U_BEC_5V_1.13 (BOOT)
BEC1_COMP: C_BEC1_COMP.1, U_BEC_5V_1.8 (COMP)
BEC1_FB: C_BEC1_COMP.2 (N), R_FB1_1.2 (B), R_FB1_2.1 (A), U_BEC_5V_1.7 (VSENSE)
BEC1_SS: C_BEC1_SS.1, U_BEC_5V_1.9 (SS/TR)
BEC1_SW: C_BEC1_BOOT.2 (N), L1.1 (A), U_BEC_5V_1.11 (PH), U_BEC_5V_1.12 (PH)
BEC2_BOOT: C_BEC2_BOOT.1, U_BEC_5V_2.13 (BOOT)
BEC2_COMP: C_BEC2_COMP.1, U_BEC_5V_2.8 (COMP)
BEC2_FB: C_BEC2_COMP.2 (N), R_FB2_1.2 (B), R_FB2_2.1 (A), U_BEC_5V_2.7 (VSENSE)
BEC2_SS: C_BEC2_SS.1, U_BEC_5V_2.9 (SS/TR)
BEC2_SW: C_BEC2_BOOT.2 (N), L2.1 (A), U_BEC_5V_2.11 (PH), U_BEC_5V_2.12 (PH)
BEC6_BOOT: C_BEC6_BOOT.1, U_BEC_6V.1 (BOOT)
BEC6_COMP: C_BEC6_COMP.1, U_BEC_6V.6 (COMP)
BEC6_FB: C_BEC6_COMP.2 (N), R_FB6_1.2 (B), R_FB6_2.1 (A), U_BEC_6V.5 (FB)
BEC6_SW: C_BEC6_BOOT.2 (N), L3.1 (A), U_BEC_6V.8 (SW)
CANFD_RX: U_ISOCAN.5 (RXD), U_MCU.17 (PA13/CAN0_RX)
CANFD_STB: R_CANSTB.1 (A), U_ISOCAN.4 (STB), U_MCU.27 (PA23/GPIO)
CANFD_TX: U_ISOCAN.3 (TXD), U_MCU.16 (PA12/CAN0_TX)
CAN_H: J_CAN_IN.1 (H), J_CAN_OUT.1 (H), R_CANTERM.1 (A), U_ISOCAN.19 (CANH)
CAN_L: J_CAN_IN.2 (L), J_CAN_OUT.2 (L), R_CANTERM.2 (B), U_ISOCAN.18 (CANL)
CELL_ALERT_N: J_ALERT.2 (ALERT_N), R_ALERT.2 (B), U_CELL.30 (ALERT)
CELL_B0: C_CAP1.2 (N), C_REGOUT.2 (N), J_BAL.1 (BAL_GND), U_CELL.27 (VC0)
CELL_B1: R_BAL1.2 (B), U_CELL.26 (VC1)
CELL_B2: R_BAL2.2 (B), U_CELL.25 (VC2)
CELL_B3: R_BAL3.2 (B), U_CELL.24 (VC3)
CELL_B4: R_BAL4.2 (B), U_CELL.23 (VC4)
CELL_B5: C_CAP2.2 (N), R_BAL5.2 (B), U_CELL.10 (VC5x), U_CELL.21 (VC5B), U_CELL.22 (VC5)
CELL_B6: R_BAL6.2 (B), U_CELL.16 (VC10), U_CELL.17 (VC9), U_CELL.18 (VC8), U_CELL.19 (VC7), U_CELL.20 (VC6)
CELL_BAL1: J_BAL.2 (B1), R_BAL1.1 (A)
CELL_BAL2: J_BAL.3 (B2), R_BAL2.1 (A)
CELL_BAL3: J_BAL.4 (B3), R_BAL3.1 (A)
CELL_BAL4: J_BAL.5 (B4), R_BAL4.1 (A)
CELL_BAL5: J_BAL.6 (B5), R_BAL5.1 (A)
CELL_BAL6: J_BAL.7 (B6), R_BAL6.1 (A)
CELL_CAP1: C_CAP1.1, U_CELL.7 (CAP1)
CELL_CAP2: C_CAP2.1, U_CELL.11 (NC), U_CELL.12 (NC), U_CELL.14 (CAP2)
CELL_CHG_GATE: Q_BATT_CHG.4 (G), U_CELL.2 (CHG)
CELL_REGOUT: C_REGOUT.1, R_NTC_PU.1 (A), U_CELL.8 (REGOUT)
ESC1_CM: CM_ESC1.2 (P1B), RS1.1 (IP), RS1.2 (IP)
ESC1_FUSED: CM_ESC1.1 (P1A), C_DEC1.1, F_ESC1.2 (B)
ESC1_OUT: ESC1_LINK.2 (B), J_ESC1.1 (+)
ESC2_CM: CM_ESC2.2 (P1B), RS2.1 (IP), RS2.2 (IP)
ESC2_FUSED: CM_ESC2.1 (P1A), C_DEC2.1, F_ESC2.2 (B)
ESC2_OUT: ESC2_LINK.2 (B), J_ESC2.1 (+)
ESC3_CM: CM_ESC3.2 (P1B), RS3.1 (IP), RS3.2 (IP)
ESC3_FUSED: CM_ESC3.1 (P1A), C_DEC3.1, F_ESC3.2 (B)
ESC3_OUT: ESC3_LINK.2 (B), J_ESC3.1 (+)
ESC4_CM: CM_ESC4.2 (P1B), RS4.1 (IP), RS4.2 (IP)
ESC4_FUSED: CM_ESC4.1 (P1A), C_DEC4.1, F_ESC4.2 (B)
ESC4_OUT: ESC4_LINK.2 (B), J_ESC4.1 (+)
GND: C_BEC1_IN.2 (N), C_BEC1_OUT1.2 (N), C_BEC1_OUT2.2 (N), C_BEC1_SS.2 (N), C_BEC2_IN.2 (N), C_BEC2_OUT1.2 (N), C_BEC2_OUT2.2 (N), C_BEC2_SS.2 (N), C_BEC_SV_IN.2 (N), C_BEC_SV_OUT1.2 (N), C_BEC_SV_OUT2.2 (N), C_ISOCAN1.2 (N), C_ISOCAN2.2 (N), C_ISOCAN3.2 (N), C_RS485_1.2 (N), C_RS485_2.2 (N), C_RS485_3.2 (N), C_TPM1.2 (N), C_TPM2.2 (N), C_TPM3.2 (N), C_TPM4.2 (N), J_5V.3 (-), J_5V.4 (-), J_6V.3 (-), J_6V.4 (-), R_CANSTB.2 (B), R_FB1_2.2 (B), R_FB2_2.2 (B), R_FB6_2.2 (B), R_GND_PGND.1 (A), U_BEC_5V_1.1 (RT/CLK), U_BEC_5V_1.2 (GND), U_BEC_5V_1.3 (GND), U_BEC_5V_1.15 (EP), U_BEC_5V_2.1 (RT/CLK), U_BEC_5V_2.2 (GND), U_BEC_5V_2.3 (GND), U_BEC_5V_2.15 (EP), U_BEC_6V.4 (RT/CLK), U_BEC_6V.7 (GND), U_BEC_6V.9 (EP), U_IS1.1 (A1), U_IS1.2 (A0), U_IS1.7 (GND), U_IS2.1 (A1), U_IS2.7 (GND), U_IS3.1 (A1), U_IS3.7 (GND), U_IS4.1 (A1), U_IS4.7 (GND), U_ISOCAN.6 (GNDIO), U_ISOCAN.10 (GND1), U_IS_MAIN.2 (A0), U_IS_MAIN.7 (GND), U_RS485.6 (GNDIO), U_RS485.10 (GND1)
I2C_SDA: D_I2C.3 (IO2), J_I2C.4 (SDA), R_I2C_SDA.2 (B), U_CELL.4 (SDA), U_IS1.4 (SDA), U_IS2.4 (SDA), U_IS3.2 (A0), U_IS3.4 (SDA), U_IS4.4 (SDA), U_IS_MAIN.4 (SDA), U_MCU.1 (PA0/I2C0_SDA)
ISO_5V_485: C_RS485_4.1, C_RS485_5.1, U_RS485.12 (VISOOUT), U_RS485.16 (VISOIN)
ISO_5V_CAN: C_ISOCAN4.1, C_ISOCAN5.1, U_ISOCAN.12 (VISOOUT), U_ISOCAN.13 (VSIN), U_ISOCAN.20 (VISOIN)
ISO_GND_485: C_RS485_4.2 (N), C_RS485_5.2 (N), J_485_IN.3 (GND), J_485_OUT.3 (GND), U_RS485.11 (GND2), U_RS485.13 (MODE), U_RS485.15 (GISOIN)
ISO_GND_CAN: C_ISOCAN4.2 (N), C_ISOCAN5.2 (N), J_CAN_IN.3 (GND), J_CAN_OUT.3 (GND), U_ISOCAN.11 (GND2), U_ISOCAN.15 (GISOIN), U_ISOCAN.16 (GISOIN), U_ISOCAN.17 (GISOIN)
J_CHASSIS_NET: C_Y1.2 (N), C_Y2.2 (N), J_CHASSIS.1, R_CHGND.1 (A)
MCU_NRST: J_SWD_H.3 (NRST), R_MCU_NRST.2 (B), U_MCU.3 (NRST)
MCU_SWCLK: J_SWD_H.2 (CLK), U_MCU.24 (PA21b/SWCLK)
MCU_SWDIO: J_SWD_H.1 (DIO), U_MCU.23 (PA20/SWDIO)
MCU_VCORE: C_MCU_VCORE.1, U_MCU.32 (VCORE)
NTC_P: C_NTC.1, J_NTC.1 (NTC+), R_NTC_PU.2 (B), U_CELL.6 (TS1)
REG3V3_FB: R_H_FBB.1, R_H_FBT.2, U_REG_3V3_H.1 (FB)
REG3V3_SW: L_H1.1 (A), U_REG_3V3_H.4 (SW)
RS485_A: J_485_IN.1 (A), J_485_OUT.1 (A), R_485TERM.1 (A), U_RS485.17 (Y), U_RS485.20 (A)
RS485_B: J_485_IN.2 (B), J_485_OUT.2 (B), R_485TERM.2 (B), U_RS485.18 (Z), U_RS485.19 (B)
RS485_DE: U_MCU.25 (PA21/GPIO), U_RS485.3 (DE), U_RS485.5 (RE)
RS485_FLT_N: R_RS485FLT_PU.2 (B), U_MCU.26 (PA22/GPIO), U_RS485.8 (EN/FLT)
RS485_RX: U_MCU.13 (PA9/UART1_RX), U_RS485.4 (R)
RS485_TX: U_MCU.12 (PA8/UART1_TX), U_RS485.2 (D)
SHUNT1_N: ESC1_LINK.1 (A), RS1.4 (SN), U_IS1.9 (IN-)
SHUNT1_P: RS1.3 (SP), U_IS1.10 (IN+)
SHUNT2_N: ESC2_LINK.1 (A), RS2.4 (SN), U_IS2.9 (IN-)
SHUNT2_P: RS2.3 (SP), U_IS2.10 (IN+)
SHUNT3_N: ESC3_LINK.1 (A), RS3.4 (SN), U_IS3.9 (IN-)
SHUNT3_P: RS3.3 (SP), U_IS3.10 (IN+)
SHUNT4_N: ESC4_LINK.1 (A), RS4.4 (SN), U_IS4.9 (IN-)
SHUNT4_P: RS4.3 (SP), U_IS4.10 (IN+)
SHUNT_MAIN_N: RS_MAIN.4 (SN), U_CELL.29 (SRN), U_IS_MAIN.9 (IN-), VDIS_LINK.1 (A)
SHUNT_MAIN_P: RS_MAIN.3 (SP), U_CELL.28 (SRP), U_IS_MAIN.10 (IN+)
TPM_P10_PU: R_TPM10.2 (B), U_TPM.10 (NCI/VDD)
TPM_PIRQ: U_MCU.7 (PA3/GPIO), U_TPM.18 (PIRQ#)
TPM_RESET_N: U_MCU.11 (PA7/GPIO), U_TPM.17 (RST#)
TPM_SPI_CS: R_TPMCS.2 (B), U_MCU.6 (PA2/SPI0_CS), U_TPM.20 (CS#)
TPM_SPI_MISO: U_MCU.8 (PA4/SPI0_MISO), U_TPM.24 (MISO)
TPM_SPI_MOSI: U_MCU.9 (PA5/SPI0_MOSI), U_TPM.21 (MOSI)
TPM_SPI_SCK: U_MCU.10 (PA6/SPI0_SCK), U_TPM.19 (SCLK)
VBAT: CM2.2 (P1B), F1.1 (A), Q_BATT_CHG.1 (S), Q_BATT_CHG.2 (S), Q_BATT_CHG.3 (S), Q_BATT_CHG.5 (D), Q_BATT_CHG.6 (D), Q_BATT_CHG.7 (D), Q_BATT_CHG.8 (D), Q_BATT_DSG.5 (D), Q_BATT_DSG.6 (D), Q_BATT_DSG.7 (D), Q_BATT_DSG.8 (D), U_CELL.9 (REGSRC), U_CELL.15 (BAT)
VBAT_F1: C1.1, C2.1, C3.1, C_DM1.1, C_Y1.1, D1.1 (A), F1.2 (B), RS_MAIN.1 (IP), RS_MAIN.2 (IP)
VDIS: FB_5V1.1 (IN), FB_5V2.1 (IN), FB_6V.1 (IN), F_ESC1.1 (A), F_ESC2.1 (A), F_ESC3.1 (A), F_ESC4.1 (A), Q_BATT_DSG.1 (S), Q_BATT_DSG.2 (S), Q_BATT_DSG.3 (S), R_EN_BIAS.1 (A), U_BEC_5V_1.4 (PVIN), U_BEC_5V_1.5 (PVIN), U_BEC_5V_1.6 (VIN), U_BEC_5V_2.4 (PVIN), U_BEC_5V_2.5 (PVIN), U_BEC_5V_2.6 (VIN), U_BEC_6V.2 (VIN), U_IS1.8 (VBUS), U_IS2.8 (VBUS), U_IS3.8 (VBUS), U_IS4.8 (VBUS), U_IS_MAIN.8 (VBUS), VDIS_LINK.2 (B)
VDIS_5V1: C_BEC1_IN.1, FB_5V1.2 (OUT)
VDIS_5V2: C_BEC2_IN.1, FB_5V2.2 (OUT)
VDIS_6V: C_BEC_SV_IN.1, FB_6V.2 (OUT)

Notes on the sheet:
WÜRTH ELEKTRONIK USAGE NOTICE (verbatim, 749010012A data sheet rev 004.000 p.1; applies to Würth parts on this board: 7440640500, 742792612): This electronic component has been designed and developed for usage in general electronic equipment only. This product is not authorized for use in equipment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

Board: 4 copper layers, 153 parts (70 on the bottom side), 107 nets, no tracks yet.
